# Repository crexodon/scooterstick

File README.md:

# scooterstick
makes e-scooter go fast

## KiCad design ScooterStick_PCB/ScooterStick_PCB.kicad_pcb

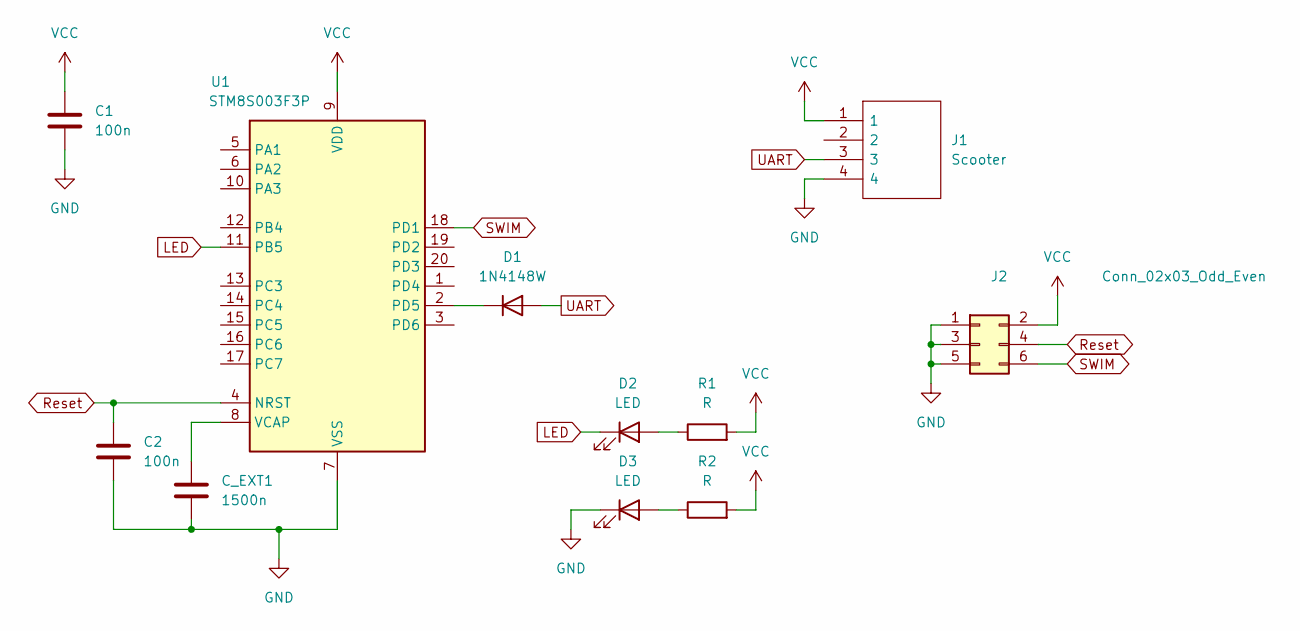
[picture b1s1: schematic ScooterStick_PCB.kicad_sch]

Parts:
C1, C2: 100n; C_0402_1005Metric_Pad0.74x0.62mm_HandSolder
C_EXT1: 1500n; C_0402_1005Metric_Pad0.74x0.62mm_HandSolder
D1: 1N4148W; D_SOD-123
D2, D3: LED; LED_0402_1005Metric_Pad0.77x0.64mm_HandSolder
J1: Scooter; HDRV4W56P0X200_1X4_800X200X749P; Mouser Part Number 575-8362200410001101
J2: Conn_02x03_Odd_Even; Tag-Connect_TC2030-IDC-NL_2x03_P1.27mm_Vertical
R1, R2: R; R_0402_1005Metric_Pad0.72x0.64mm_HandSolder
U1: STM8S003F3P; TSSOP-20_4.4x6.5mm_P0.65mm

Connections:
GND: C1.2, C2.2, C_EXT1.2, D3.1 (K), J1.4, J2.1, J2.3, J2.5, U1.7 (VSS)
LED: D2.1 (K), U1.11 (PB5)
unnamed: C_EXT1.1, U1.8 (VCAP)
unnamed: D1.1 (K), U1.2 (PD5)
unnamed: D2.2 (A), R1.1
unnamed: D3.2 (A), R2.1
Reset: C2.1, J2.4, U1.4 (NRST)
SWDIO: J2.6, U1.18 (PD1)
UART: D1.2 (A), J1.3
VCC: C1.1, J1.1, J2.2, R1.2, R2.2, U1.9 (VDD)

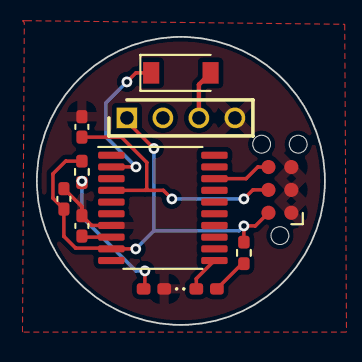
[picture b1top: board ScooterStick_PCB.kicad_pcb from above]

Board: 2 copper layers, 16.0 x 16.0 mm, 11 parts (0 on the bottom side), 10 nets.
